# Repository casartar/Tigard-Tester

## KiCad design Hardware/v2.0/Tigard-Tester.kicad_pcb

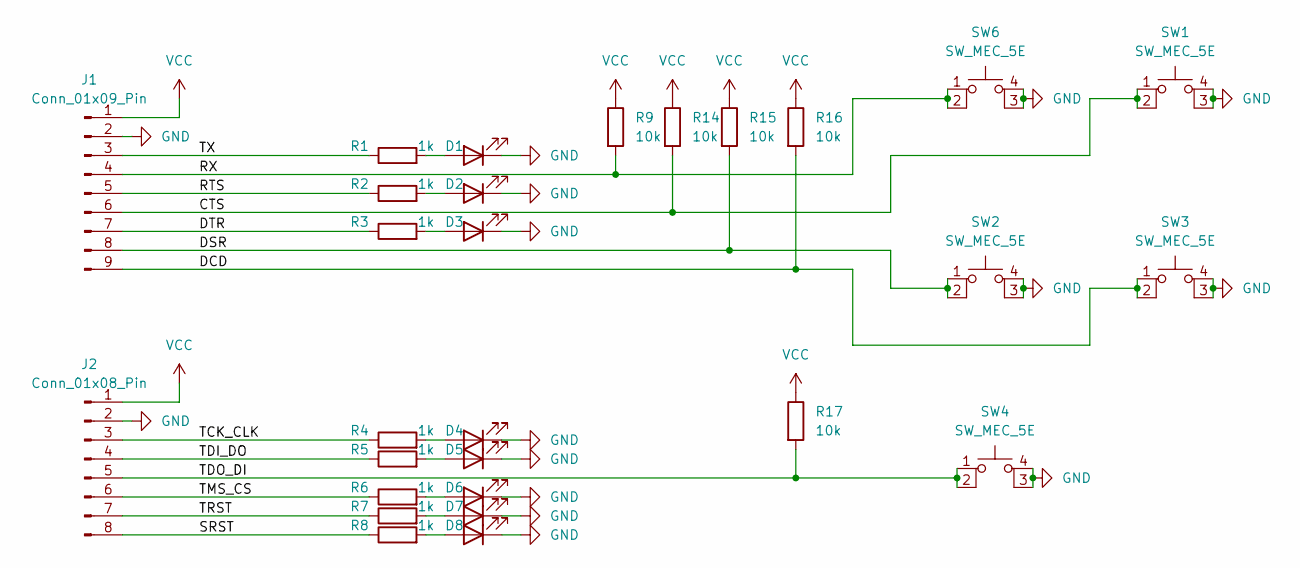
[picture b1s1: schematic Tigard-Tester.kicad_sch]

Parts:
D1, D2, D3, D4, D5, D6, D7, D8: LED; LED_0805_2012Metric_Pad1.15x1.40mm_HandSolder; LCSC C94868
J1: Conn_01x09_Pin; PinHeader_1x09_P2.54mm_Horizontal; LCSC C492417
J2: Conn_01x08_Pin; PinHeader_1x08_P2.54mm_Horizontal; LCSC C492416
R1, R2, R3, R4, R5, R6, R7, R8: 1k; R_0805_2012Metric_Pad1.20x1.40mm_HandSolder; LCSC C95781
R9, R14, R15, R16, R17: 10k; R_0805_2012Metric_Pad1.20x1.40mm_HandSolder; LCSC C84376
SW1, SW2, SW3, SW4, SW6: SW_MEC_5E; KH-6X6X6H-STM

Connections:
/CTS: J1.6, R14.2, SW1.1, SW1.2
/DCD: J1.9, R16.2, SW3.1, SW3.2
/DSR: J1.8, R15.2, SW2.1, SW2.2
/DTR: J1.7, R3.1
/RTS: J1.5, R2.1
/RX: J1.4, R9.2, SW6.1, SW6.2
/SRST: J2.8, R8.1
/TCK_CLK: J2.3, R4.1
/TDI_DO: J2.4, R5.1
/TDO_DI: J2.5, R17.2, SW4.1, SW4.2
/TMS_CS: J2.6, R6.1
/TRST: J2.7, R7.1
/TX: J1.3, R1.1
GND: D1.1 (K), D2.1 (K), D3.1 (K), D4.1 (K), D5.1 (K), D6.1 (K), D7.1 (K), D8.1 (K), J1.2, J2.2, SW1.3 (K), SW1.4 (A), SW2.3 (K), SW2.4 (A), SW3.3 (K), SW3.4 (A), SW4.3 (K), SW4.4 (A), SW6.3 (K), SW6.4 (A)
unnamed: D1.2 (A), R1.2
unnamed: D2.2 (A), R2.2
unnamed: D3.2 (A), R3.2
unnamed: D4.2 (A), R4.2
unnamed: D5.2 (A), R5.2
unnamed: D6.2 (A), R6.2
unnamed: D7.2 (A), R7.2
unnamed: D8.2 (A), R8.2
VCC: J1.1, J2.1, R9.1, R14.1, R15.1, R16.1, R17.1

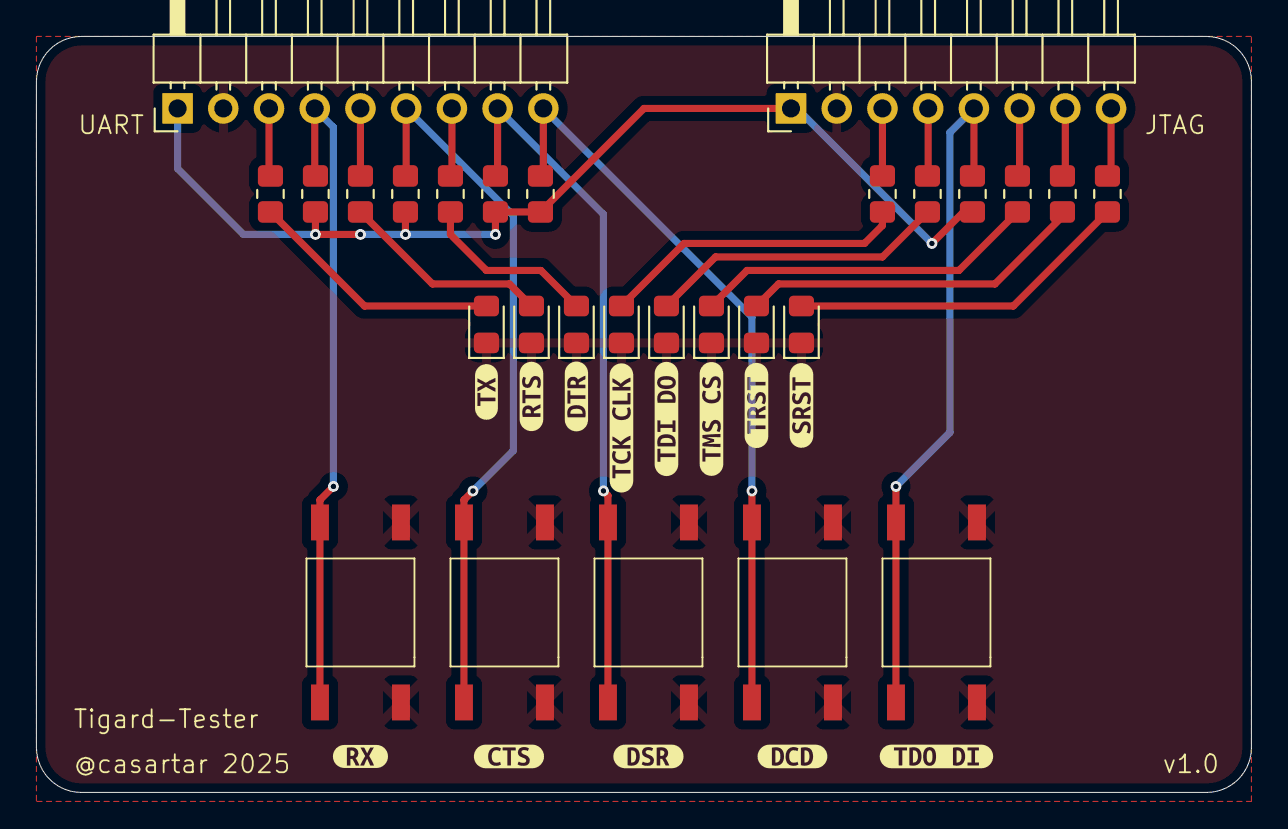
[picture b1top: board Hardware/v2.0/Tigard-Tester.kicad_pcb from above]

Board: 2 copper layers, 67.5 x 42.0 mm, 41 parts (0 on the bottom side), 23 nets.

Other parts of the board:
kibuzzard-686248A1: G***; kibuzzard-686248A1
kibuzzard-686248AA: G***; kibuzzard-686248AA
kibuzzard-686248B5: G***; kibuzzard-686248B5
kibuzzard-686248C0: G***; kibuzzard-686248C0
kibuzzard-686248CF: G***; kibuzzard-686248CF
kibuzzard-686248E6: G***; kibuzzard-686248E6
kibuzzard-686248FB: G***; kibuzzard-686248FB
kibuzzard-6862490B: G***; kibuzzard-6862490B
kibuzzard-6862493A: G***; kibuzzard-6862493A
kibuzzard-68624870: G***; kibuzzard-68624870
kibuzzard-68624879: G***; kibuzzard-68624879
kibuzzard-68624893: G***; kibuzzard-68624893
kibuzzard-68624928: G***; kibuzzard-68624928

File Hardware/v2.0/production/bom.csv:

Designator,Footprint,Quantity,Value,LCSC Part #
"D1, D2, D3, D4, D5, D6, D7, D8",0805,8,LED,C94868
J1,PinHeader_1x09_P2.54mm_Horizontal,1,Conn_01x09_Pin,C492417
J2,PinHeader_1x08_P2.54mm_Horizontal,1,Conn_01x08_Pin,C492416
"R1, R2, R3, R4, R5, R6, R7, R8",0805,8,1k,C95781
"R14, R9",0805,2,10k, C84376 
"R15, R16, R17",0805,3,10k, C84376
"SW1, SW2, SW3, SW4, SW6",KH-6X6X6H-STM,5,SW_MEC_5E,

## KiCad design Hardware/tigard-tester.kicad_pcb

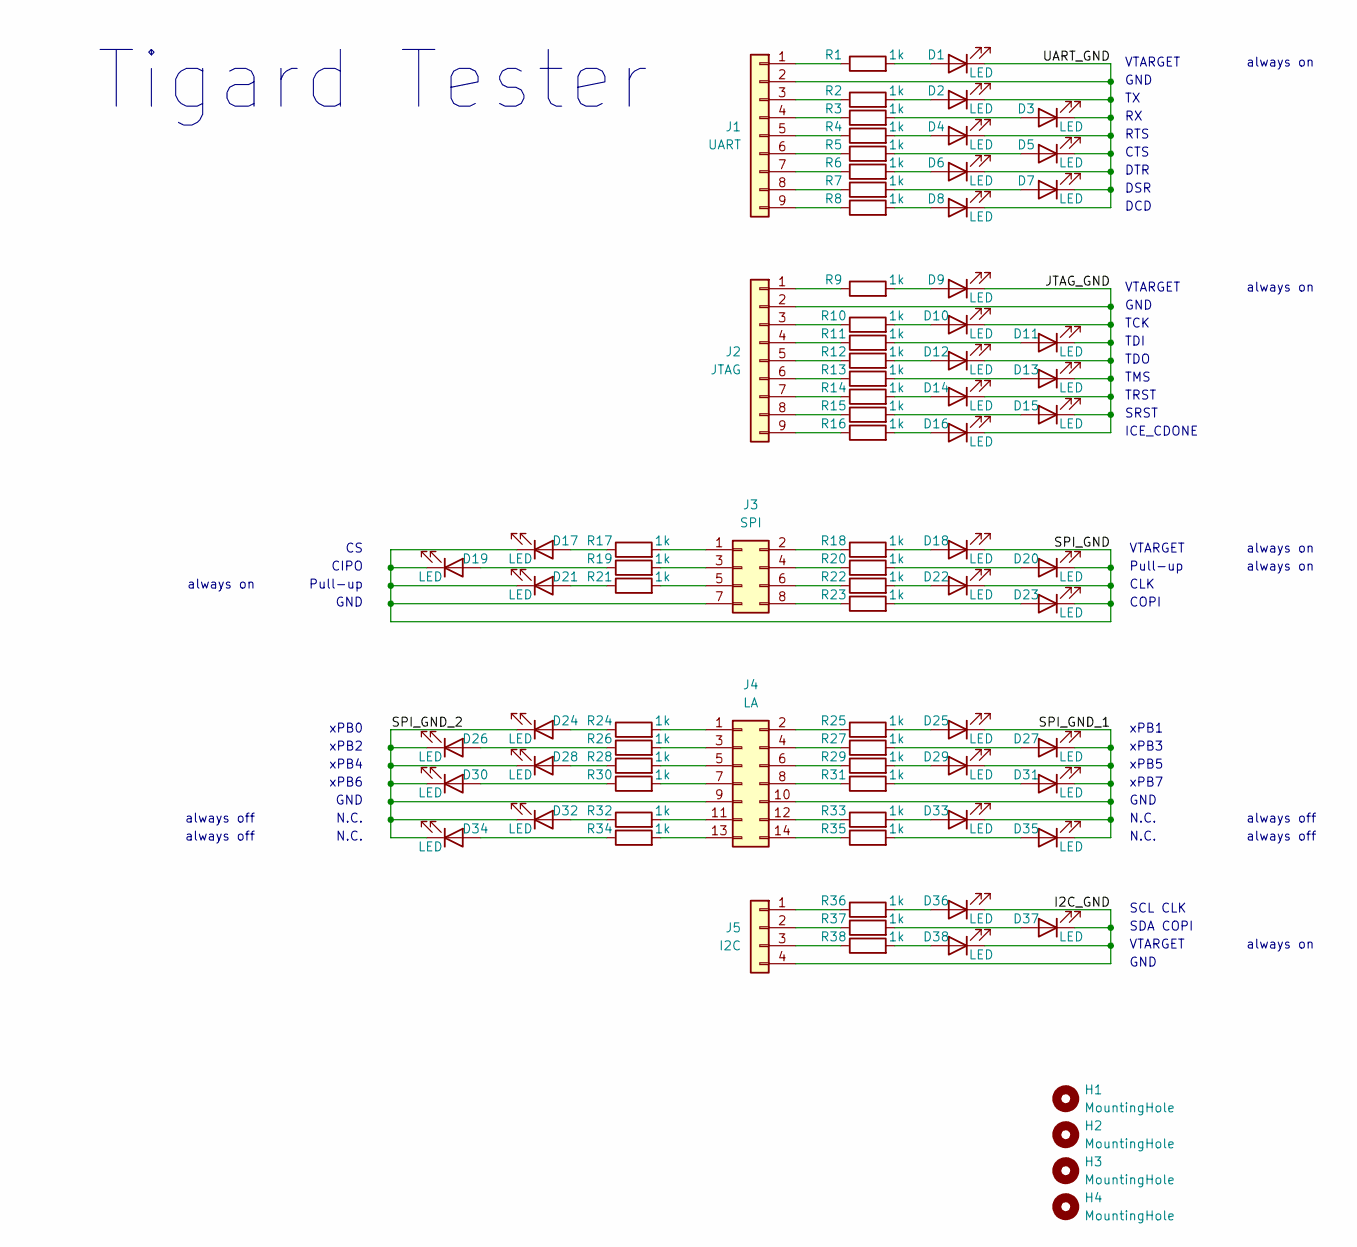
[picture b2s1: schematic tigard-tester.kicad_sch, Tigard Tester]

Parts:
D1, D2, D3, D4, D5, D6, D7, D8, D9, D10, D11, D12, D13, D14, D15, D16, D17, D18, D19, D20, D21, D22, D23, D24, D25, D26, D27, D28, D29, D30, D31, D32, D33, D34, D35, D36, D37, D38: LED; LED_0805_2012Metric_Pad1.15x1.40mm_HandSolder
H1, H2, H3, H4: MountingHole; MountingHole_3.2mm_M3
J1: UART; PinHeader_1x09_P2.54mm_Vertical
J2: JTAG; PinHeader_1x09_P2.54mm_Vertical
J3: SPI; PinHeader_2x04_P2.54mm_Vertical
J4: LA; PinHeader_2x07_P1.27mm_Vertical_SMD
J5: I2C; PinSocket_1x04_P2.54mm_Vertical
R1, R2, R3, R4, R5, R6, R7, R8, R9, R10, R11, R12, R13, R14, R15, R16, R17, R18, R19, R20, R21, R22, R23, R24, R25, R26, R27, R28, R29, R30, R31, R32, R33, R34, R35, R36, R37, R38: 1k; R_0805_2012Metric_Pad1.20x1.40mm_HandSolder

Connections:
/I2C_GND: D36.1 (K), D37.1 (K), D38.1 (K), J5.4
/JTAG_GND: D9.1 (K), D10.1 (K), D11.1 (K), D12.1 (K), D13.1 (K), D14.1 (K), D15.1 (K), D16.1 (K), J2.2
/SPI_GND: D17.1 (K), D18.1 (K), D19.1 (K), D20.1 (K), D21.1 (K), D22.1 (K), D23.1 (K), J3.7
/SPI_GND_1: D25.1 (K), D27.1 (K), D29.1 (K), D31.1 (K), D33.1 (K), D35.1 (K), J4.10
/SPI_GND_2: D24.1 (K), D26.1 (K), D28.1 (K), D30.1 (K), D32.1 (K), D34.1 (K), J4.9
/UART_GND: D1.1 (K), D2.1 (K), D3.1 (K), D4.1 (K), D5.1 (K), D6.1 (K), D7.1 (K), D8.1 (K), J1.2
unnamed: D1.2 (A), R1.2
unnamed: D2.2 (A), R2.2
unnamed: D3.2 (A), R3.2
unnamed: D4.2 (A), R4.2
unnamed: D5.2 (A), R5.2
unnamed: D6.2 (A), R6.2
unnamed: D7.2 (A), R7.2
unnamed: D8.2 (A), R8.2
unnamed: D9.2 (A), R9.2
unnamed: D10.2 (A), R10.2
unnamed: D11.2 (A), R11.2
unnamed: D12.2 (A), R12.2
unnamed: D13.2 (A), R13.2
unnamed: D14.2 (A), R14.2
unnamed: D15.2 (A), R15.2
unnamed: D16.2 (A), R16.2
unnamed: D17.2 (A), R17.1
unnamed: D18.2 (A), R18.2
unnamed: D19.2 (A), R19.1
unnamed: D20.2 (A), R20.2
unnamed: D21.2 (A), R21.1
unnamed: D22.2 (A), R22.2
unnamed: D23.2 (A), R23.2
unnamed: D24.2 (A), R24.1
unnamed: D25.2 (A), R25.2
unnamed: D26.2 (A), R26.1
unnamed: D27.2 (A), R27.2
unnamed: D28.2 (A), R28.1
unnamed: D29.2 (A), R29.2
unnamed: D30.2 (A), R30.1
unnamed: D31.2 (A), R31.2
unnamed: D32.2 (A), R32.1
unnamed: D33.2 (A), R33.2
unnamed: D34.2 (A), R34.1
unnamed: D35.2 (A), R35.2
unnamed: D36.2 (A), R36.2
unnamed: D37.2 (A), R37.2
unnamed: D38.2 (A), R38.2
unnamed: J1.1, R1.1
unnamed: J1.3, R2.1
unnamed: J1.4, R3.1
unnamed: J1.5, R4.1
unnamed: J1.6, R5.1
unnamed: J1.7, R6.1
unnamed: J1.8, R7.1
unnamed: J1.9, R8.1
unnamed: J2.1, R9.1
unnamed: J2.3, R10.1
unnamed: J2.4, R11.1
unnamed: J2.5, R12.1
unnamed: J2.6, R13.1
unnamed: J2.7, R14.1
unnamed: J2.8, R15.1
unnamed: J2.9, R16.1
unnamed: J3.1, R17.2
unnamed: J3.2, R18.1
unnamed: J3.3, R19.2
unnamed: J3.4, R20.1
unnamed: J3.5, R21.2
unnamed: J3.6, R22.1
unnamed: J3.8, R23.1
unnamed: J4.1, R24.2
unnamed: J4.2, R25.1
unnamed: J4.3, R26.2
unnamed: J4.4, R27.1
unnamed: J4.5, R28.2
unnamed: J4.6, R29.1
unnamed: J4.7, R30.2
unnamed: J4.8, R31.1
unnamed: J4.11, R32.2
unnamed: J4.12, R33.1
unnamed: J4.13, R34.2
unnamed: J4.14, R35.1
unnamed: J5.1, R36.1
unnamed: J5.2, R37.1
unnamed: J5.3, R38.1

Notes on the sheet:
RTS
ICE_CDONE
Tigard Tester
N.C.
Pull-up
VTARGET
xPB7
DSR
always on
TRST
always off
GND
DTR
SDA COPI
COPI
SCL CLK
SRST
TDO
xPB6
TCK
TMS
xPB5
TDI
CIPO
CTS
CLK
xPB3
xPB2
xPB4
xPB0
DCD
xPB1

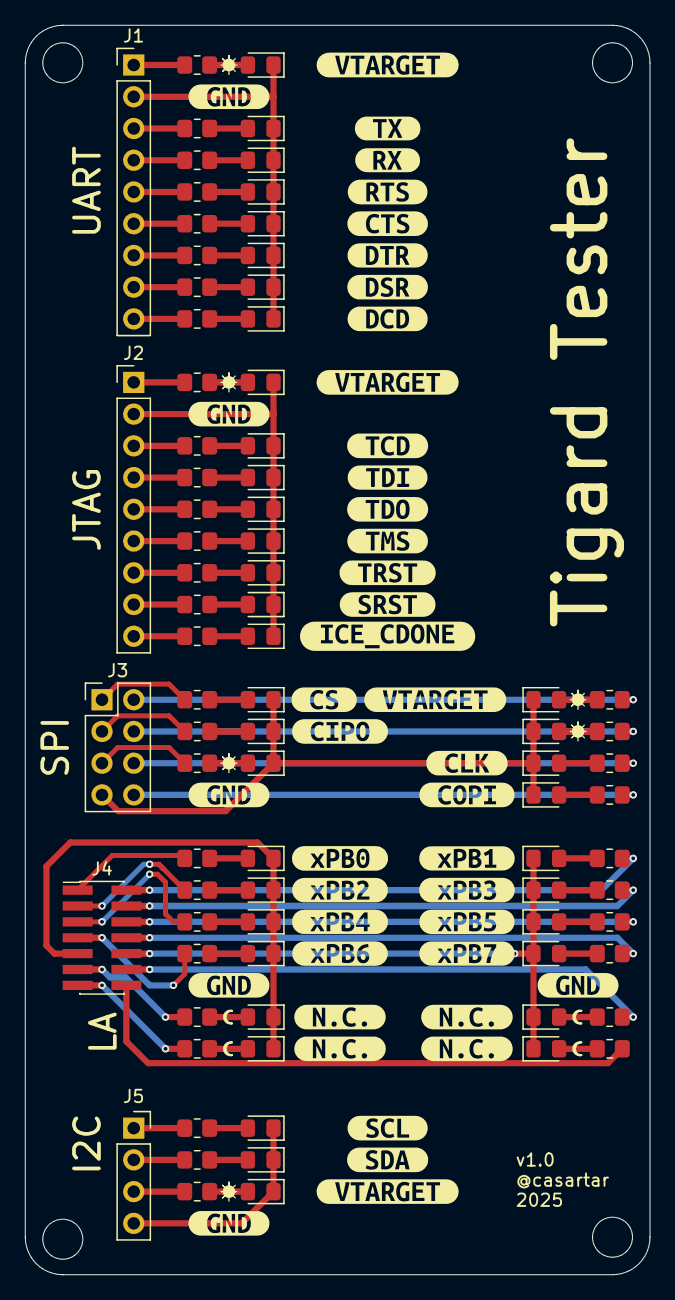
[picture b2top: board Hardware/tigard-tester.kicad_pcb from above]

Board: 2 copper layers, 50.0 x 100.0 mm, 127 parts (0 on the bottom side), 82 nets.

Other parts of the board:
kibuzzard-6782A1AC: G***; kibuzzard-6782A1AC
kibuzzard-6782A1B7: G***; kibuzzard-6782A1B7
kibuzzard-6782A1C4: G***; kibuzzard-6782A1C4
kibuzzard-6782A1D3: G***; kibuzzard-6782A1D3
kibuzzard-6782A1ED: G***; kibuzzard-6782A1ED
kibuzzard-6782A1FC: G***; kibuzzard-6782A1FC
kibuzzard-6782A2BB: G***; kibuzzard-6782A2BB
kibuzzard-6782A2CB: G***; kibuzzard-6782A2CB
kibuzzard-6782A2E4: G***; kibuzzard-6782A2E4
kibuzzard-6782A5EC: G***; kibuzzard-6782A5EC
kibuzzard-6782A18A, kibuzzard-6782A18A#2, kibuzzard-6782A18A#3, kibuzzard-6782A18A#4, kibuzzard-6782A18A#5, kibuzzard-6782A18A#6: G***; kibuzzard-6782A18A
kibuzzard-6782A20A: G***; kibuzzard-6782A20A
kibuzzard-6782A23E: G***; kibuzzard-6782A23E
kibuzzard-6782A58D: G***; kibuzzard-6782A58D
kibuzzard-6782A59C: G***; kibuzzard-6782A59C
kibuzzard-6782A62E: G***; kibuzzard-6782A62E
kibuzzard-6782A63C: G***; kibuzzard-6782A63C
kibuzzard-6782A68A: G***; kibuzzard-6782A68A
kibuzzard-6782A90E: G***; kibuzzard-6782A90E
kibuzzard-6782A92D: G***; kibuzzard-6782A92D
kibuzzard-6782A158, kibuzzard-6782A158#2, kibuzzard-6782A158#3: G***; kibuzzard-6782A158
kibuzzard-6782A238: G***; kibuzzard-6782A238
kibuzzard-6782A293: G***; kibuzzard-6782A293
kibuzzard-6782A299: G***; kibuzzard-6782A299
kibuzzard-6782A342: G***; kibuzzard-6782A342
kibuzzard-6782A349: G***; kibuzzard-6782A349
kibuzzard-6782A593: G***; kibuzzard-6782A593
kibuzzard-6782A634: G***; kibuzzard-6782A634
kibuzzard-6782A685: G***; kibuzzard-6782A685
kibuzzard-6782A691: G***; kibuzzard-6782A691
kibuzzard-6782A697: G***; kibuzzard-6782A697
kibuzzard-6782BFBD, kibuzzard-6782BFBD#2, kibuzzard-6782BFBD#3, kibuzzard-6782BFBD#4: G***; kibuzzard-6782BFBD

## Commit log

2025-01-11 create tigard tester pcb
2025-01-11 hardware finished
2025-01-11 n.c. added
2025-02-02 add assortment label
2025-02-02 update assortment label
2025-07-06 tigard tester v2.0 release
2025-07-06 remove unused test script
2025-07-06 add bom
2025-07-06 add production files
